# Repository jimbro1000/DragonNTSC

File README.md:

# NTSC VIDEO BOARD FOR DRAGON 32 RECREATION Rev 3 #

To further improve video quality on the Dragon 32 this
board completely isolates the video circuits from the rest
of the Dragon by making it a plugin. This also means that
only a single version of the Dragon rev 3 board is needed to
provide a PAL or NTSC solution.

## Progress ##

This is a complete first hack at the design, based on the
reference design in the 6847 datasheet with supporting
information from the MC1372 datasheet.

The generator and amplifier circuits are isolated and
*should* be good for a clean video signal.

## Note ##

Given most modern TVs work with NTSC **and** PAL, switching
automatically, this slimline video board (compared to the PAL
version of the board) should be a cheaper and more attractive
option. The component count is *much* lower and the harder to
find analogue multiplexer is not needed.

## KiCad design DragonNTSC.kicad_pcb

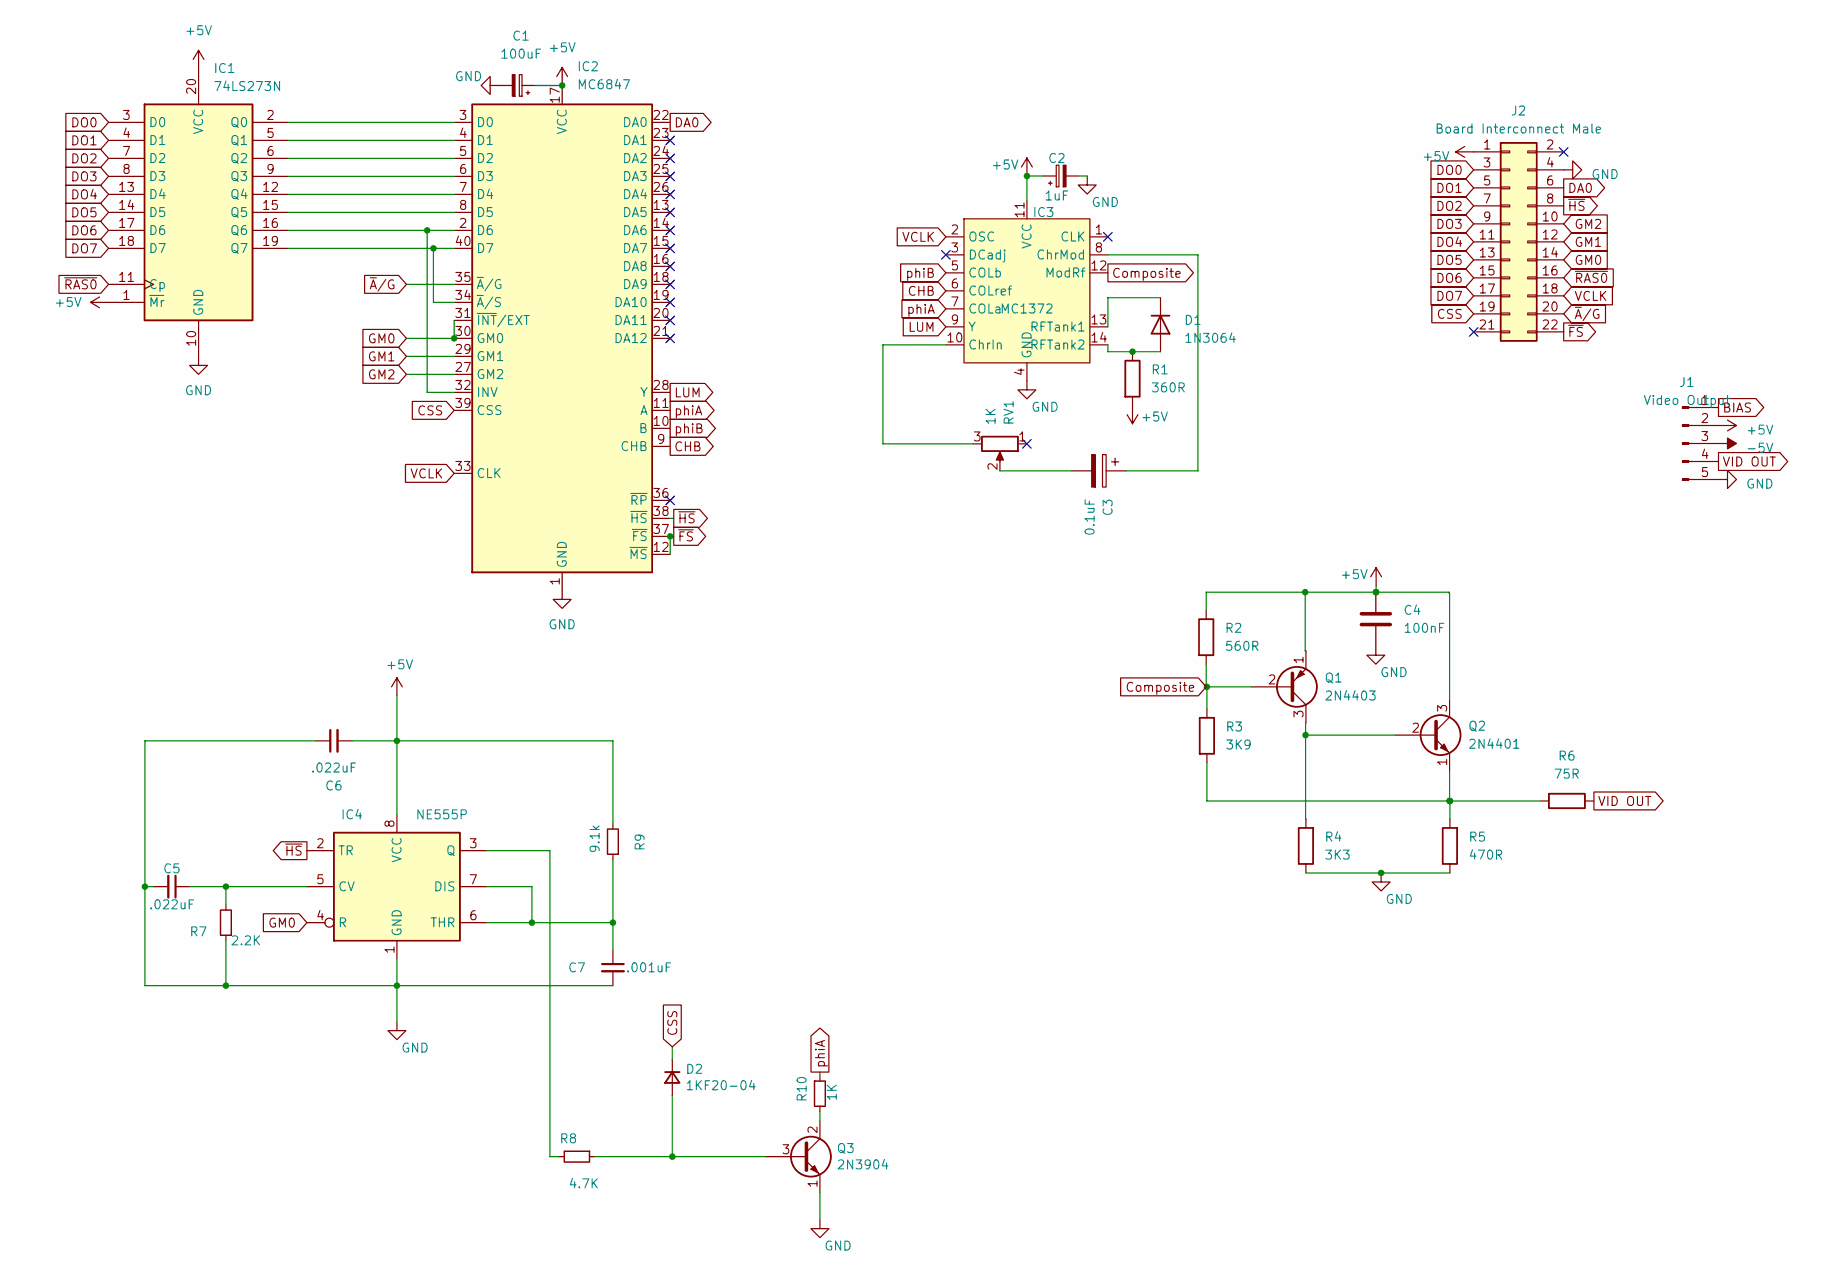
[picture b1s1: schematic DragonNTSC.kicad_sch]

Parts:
C1: 100uF; CP_Radial_D6.3mm_P2.50mm; DigiKey 732-8598-1-ND
C2: 1uF; CP_Radial_D5.0mm_P2.50mm; DigiKey 478-8984-1-ND
C3: 0.1uF; CP_Radial_D4.0mm_P2.00mm
C4: 100nF; C_Disc_D4.3mm_W1.9mm_P5.00mm
C5, C6: .022uF; C_Disc_D8.0mm_W2.5mm_P5.00mm; Manufacturer part# C317C223M5U5TA7301
C7: .001uF; C_Rect_L4.0mm_W2.5mm_P2.50mm; Manufacturer part# C315C102K1R5TA7301
D1: 1N3064; D_DO-35_SOD27_P7.62mm_Horizontal
D2: 1KF20-04; D_A-405_P10.16mm_Horizontal; Manufacturer part# 1N4148
IC1: 74LS273N; DIP-20_W7.62mm; DigiKey 296-1657-5-ND
IC2: MC6847; DIP-40_W15.24mm
IC3: MC1372; DIP-14_W7.62mm
IC4: NE555P; DIP-8_W7.62mm; Manufacturer part# A 08-LC-TT
J1: Video Output; PinHeader_1x05_P2.54mm_Vertical
J2: Board Interconnect Male; PinHeader_2x11_P2.54mm_Vertical
Q1: 2N4403; TO-92_Inline_Wide
Q2: 2N4401; TO-92_Inline_Wide
Q3: 2N3904; TO-92_Inline; Manufacturer part# PN2222A PBFREE
R1: 360R; R_Axial_DIN0207_L6.3mm_D2.5mm_P2.54mm_Vertical
R2: 560R; R_Axial_DIN0207_L6.3mm_D2.5mm_P2.54mm_Vertical
R3: 3K9; R_Axial_DIN0207_L6.3mm_D2.5mm_P2.54mm_Vertical
R4: 3K3; R_Axial_DIN0207_L6.3mm_D2.5mm_P2.54mm_Vertical
R5: 470R; R_Axial_DIN0207_L6.3mm_D2.5mm_P2.54mm_Vertical
R6: 75R; R_Axial_DIN0207_L6.3mm_D2.5mm_P2.54mm_Vertical
R7: 2.2K; R_Axial_DIN0207_L6.3mm_D2.5mm_P2.54mm_Vertical; Manufacturer part# MFR-25FRF52-2K2
R8: 4.7K; R_Axial_DIN0207_L6.3mm_D2.5mm_P2.54mm_Vertical; Manufacturer part# Stackpole Electronics Inc
R9: 9.1k; R_Axial_DIN0207_L6.3mm_D2.5mm_P2.54mm_Vertical; Manufacturer part# CF14JT9K10
R10: 1K; R_Axial_DIN0207_L6.3mm_D2.5mm_P2.54mm_Vertical; Manufacturer part# CF14JT1K00
RV1: 1K; Potentiometer_Bourns_3296W_Vertical

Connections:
+5V: C1.1, C2.1, C4.1, C6.2, IC1.1 (~Mr), IC1.20 (VCC), IC2.17 (VCC), IC3.11 (VCC), IC4.8 (VCC), J1.2, J2.1, Q1.1 (E), Q2.3 (C), R1.2, R2.1, R9.2
-5V: J1.3
BIAS: J1.1
CHB: IC2.9 (CHB), IC3.6 (COLref)
CSS: D2.1 (K), IC2.39 (CSS), J2.19
Composite: IC3.12 (ModRf), Q1.2 (B), R2.2, R3.1
DA0: IC2.22 (DA0), J2.6
DO0: IC1.3 (D0), J2.3
DO1: IC1.4 (D1), J2.5
DO2: IC1.7 (D2), J2.7
DO3: IC1.8 (D3), J2.9
DO4: IC1.13 (D4), J2.11
DO5: IC1.14 (D5), J2.13
DO6: IC1.17 (D6), J2.15
DO7: IC1.18 (D7), J2.17
GM0: IC2.30 (GM0), IC2.31 (~INT/EXT), IC4.4 (R), J2.14
GM1: IC2.29 (GM1), J2.12
GM2: IC2.27 (GM2), J2.10
GND: C1.2, C2.2, C4.2, C5.2, C6.1, C7.2, IC1.10 (GND), IC2.1 (GND), IC3.4 (GND), IC4.1 (GND), J1.5, J2.4, Q3.1 (E), R4.1, R5.1, R7.1
LUM: IC2.28 (Y), IC3.9 (Y)
unnamed: C3.2, RV1.2
unnamed: D1.2 (A), IC3.14 (RFTank2), R1.1
unnamed: D1.1 (K), IC3.13 (RFTank1)
unnamed: D2.2 (A), Q3.3 (B), R8.1
unnamed: IC1.2 (Q0), IC2.3 (D0)
unnamed: IC1.5 (Q1), IC2.4 (D1)
unnamed: IC1.6 (Q2), IC2.5 (D2)
unnamed: IC1.9 (Q3), IC2.6 (D3)
unnamed: IC1.12 (Q4), IC2.7 (D4)
unnamed: IC1.15 (Q5), IC2.8 (D5)
unnamed: IC1.16 (Q6), IC2.2 (D6), IC2.32 (INV)
unnamed: IC1.19 (Q7), IC2.34 (~A/S), IC2.40 (D7)
unnamed: IC3.10 (ChrIn), RV1.3
unnamed: C3.1, IC3.8 (ChrMod)
unnamed: C5.1, IC4.5 (CV), R7.2
unnamed: C7.1, IC4.6 (THR), IC4.7 (DIS), R9.1
unnamed: IC4.3 (Q), R8.2
unnamed: Q1.3 (C), Q2.2 (B), R4.2
unnamed: Q2.1 (E), R3.2, R5.2, R6.2
unnamed: Q3.2 (C), R10.2
VCLK: IC2.33 (CLK), IC3.2 (OSC), J2.18
VID OUT: J1.4, R6.1
phiA: IC2.11 (A), IC3.7 (COLa), R10.1
phiB: IC2.10 (B), IC3.5 (COLb)
~A/G: IC2.35 (~A/G), J2.20
~FS: IC2.12 (~MS), IC2.37 (~FS), J2.22
~HS: IC2.38 (~HS), IC4.2 (TR), J2.8
~RAS0: IC1.11 (Cp), J2.16

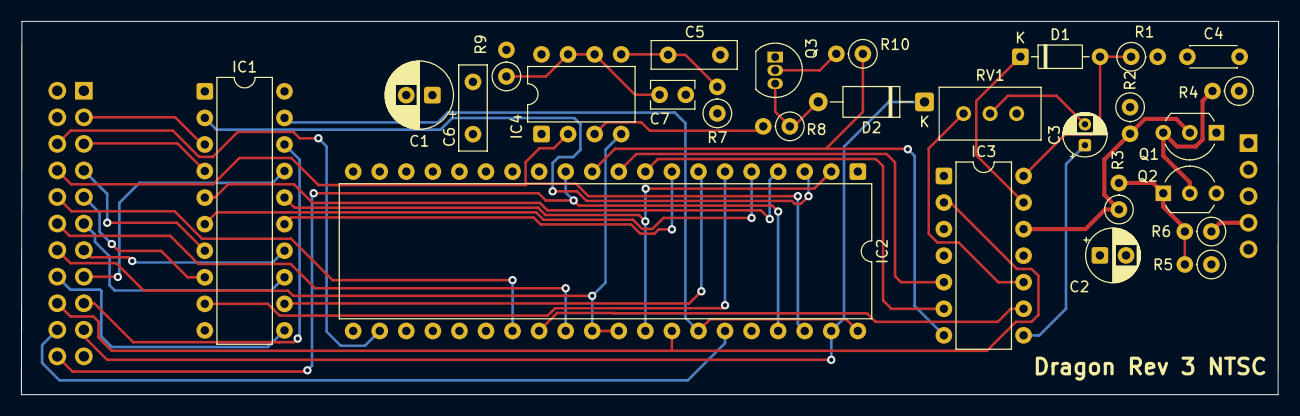
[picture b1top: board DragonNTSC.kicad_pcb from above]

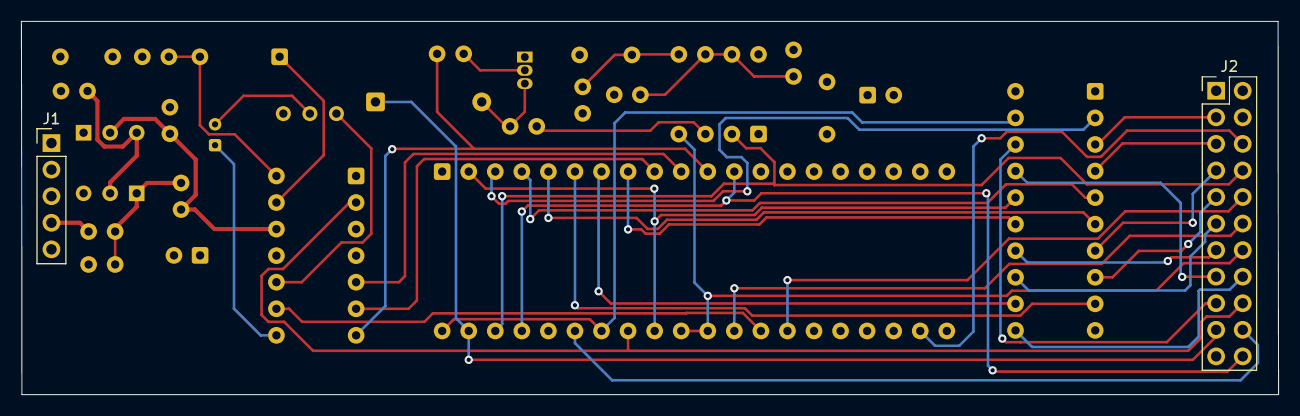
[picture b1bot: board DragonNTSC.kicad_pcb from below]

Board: 4 copper layers, 120.2 x 35.7 mm, 29 parts (2 on the bottom side), 46 nets.

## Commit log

2023-05-31 add render to readme
2023-06-01 add missing css and fs lines
2023-06-01 update render
2023-10-02 complete tracing for fabrication
2023-11-13 prepare alpha2 build
2024-02-22 prototype experiment board
2024-02-27 refine board
2024-03-02 add 555 timer
2024-03-04 move -5v
2024-03-05 add decoration
2025-11-22 migrate to kicad 9
2025-11-22 revise for fab
